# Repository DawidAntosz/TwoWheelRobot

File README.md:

# TwoWheelRobot
Differential wheeled robot

This project is focused on building a two-wheel differential robot with the ability to control and navigate in area.

## Project Structure
The project is organized into the following directories:

- `src/`: Contains the source code for the project.
  - `arduino/`: Source code using the Arduino framework (PlatformIO).
  - `esp_rtos_sdk/`: (For future development of the project using the ESP8266 RTOS SDK).

##### Control page:
<p align="center">
<!--     -->
   
<!--     -->
</p>

##### Robot V1:

##### Math model

$$
\dot{x} = \frac{R}{2}(v_r + v_\ell)\cos\phi
$$
$$
\dot{y} = \frac{R}{2}(v_r + v_\ell)\sin\phi
$$
$$
\dot{\phi} = \frac{R}{L}(v_r - v_\ell)
$$

$$
\dot{x} = v\cos\phi
$$
$$
\dot{y} = v\sin\phi
$$
$$
\dot{\phi} = \omega
$$

$$
v = \frac{R}{2}(v_r + v_\ell) \implies \frac{2v}{R} = v_r + v_\ell
$$

$$
\omega = \frac{R}{L}(v_r - v_\ell) \implies \frac{\omega L}{R} = v_r - v_\ell
$$

$$
\ v_r = \\frac{2v + \\omega L}{2R} \\\ 
$$
$$
 v_l = \\frac{2v - \\omega L}{2R} \
$$

Description parameters:
- \( v_r \): the speed of the right wheel
- \( v_\ell \): the speed of the left wheel
- \( R \): the radius of the wheel
- \( L \): the distance between the wheels
- \( $$\omega$$ \): the angular velocity of the robot

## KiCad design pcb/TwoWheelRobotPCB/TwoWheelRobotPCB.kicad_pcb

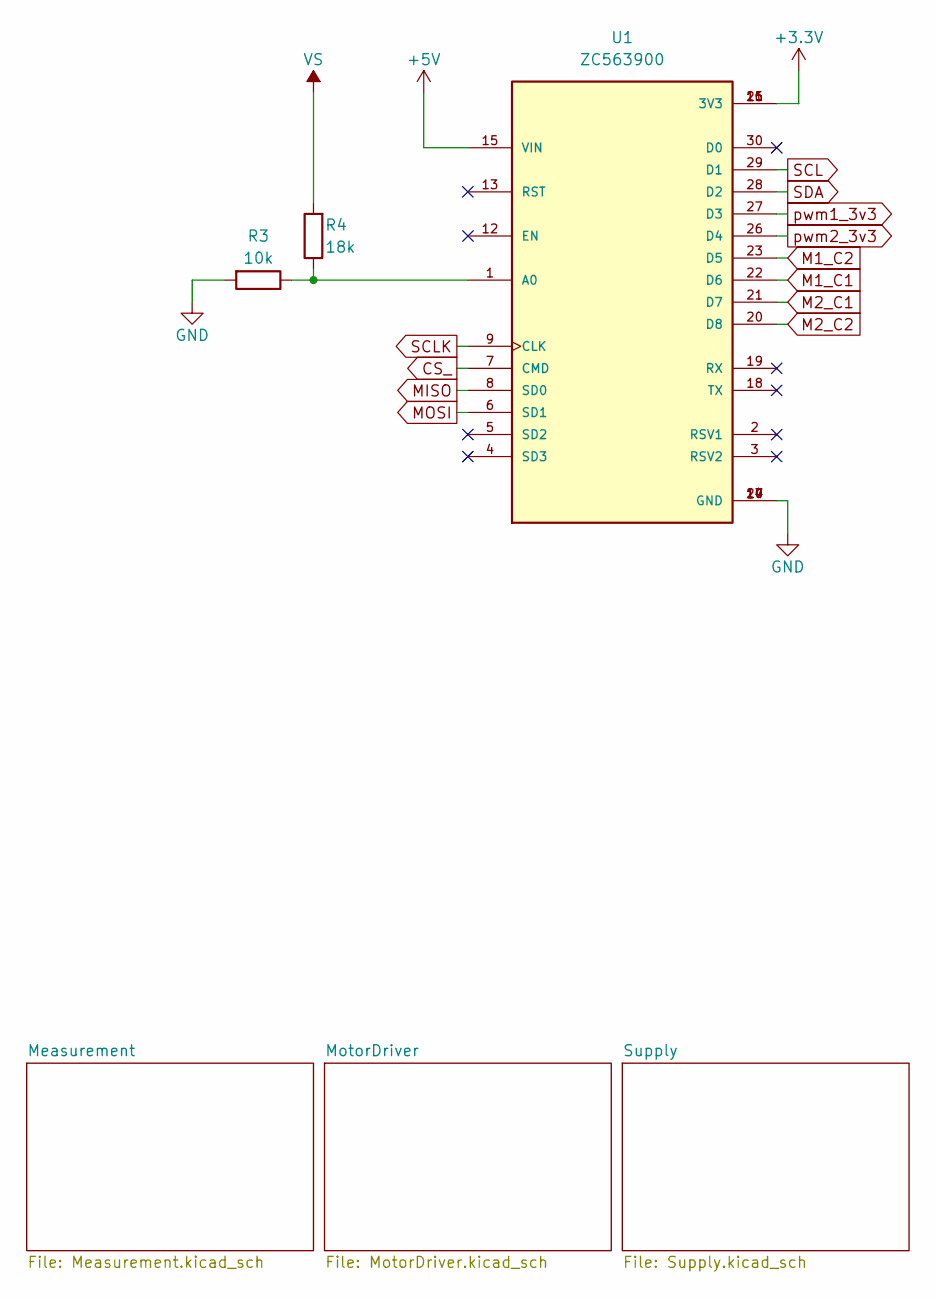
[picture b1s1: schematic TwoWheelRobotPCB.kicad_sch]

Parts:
R3: 10k; R_0805_2012Metric
R4: 18k; R_0805_2012Metric
U1: ZC563900; MODULE_ZC563900; PARTREV 1.0

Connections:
+3V3: U1.11 (3V3), U1.16 (3V3), U1.25 (3V3); also elsewhere on the board
+5V: U1.15 (VIN); also elsewhere on the board
CS_: U1.7 (CMD); also elsewhere on the board
GND: R3.2, U1.10 (GND), U1.14 (GND), U1.17 (GND), U1.24 (GND); also elsewhere on the board
M1_C1: U1.22 (D6); also elsewhere on the board
M1_C2: U1.23 (D5); also elsewhere on the board
M2_C1: U1.21 (D7); also elsewhere on the board
M2_C2: U1.20 (D8); also elsewhere on the board
MISO: U1.8 (SD0); also elsewhere on the board
MOSI: U1.6 (SD1); also elsewhere on the board
unnamed: R3.1, R4.1, U1.1 (A0)
SCL: U1.29 (D1); also elsewhere on the board
SCLK: U1.9 (CLK); also elsewhere on the board
SDA: U1.28 (D2); also elsewhere on the board
VS: R4.2; also elsewhere on the board
pwm1_3v3: U1.27 (D3); also elsewhere on the board
pwm2_3v3: U1.26 (D4); also elsewhere on the board

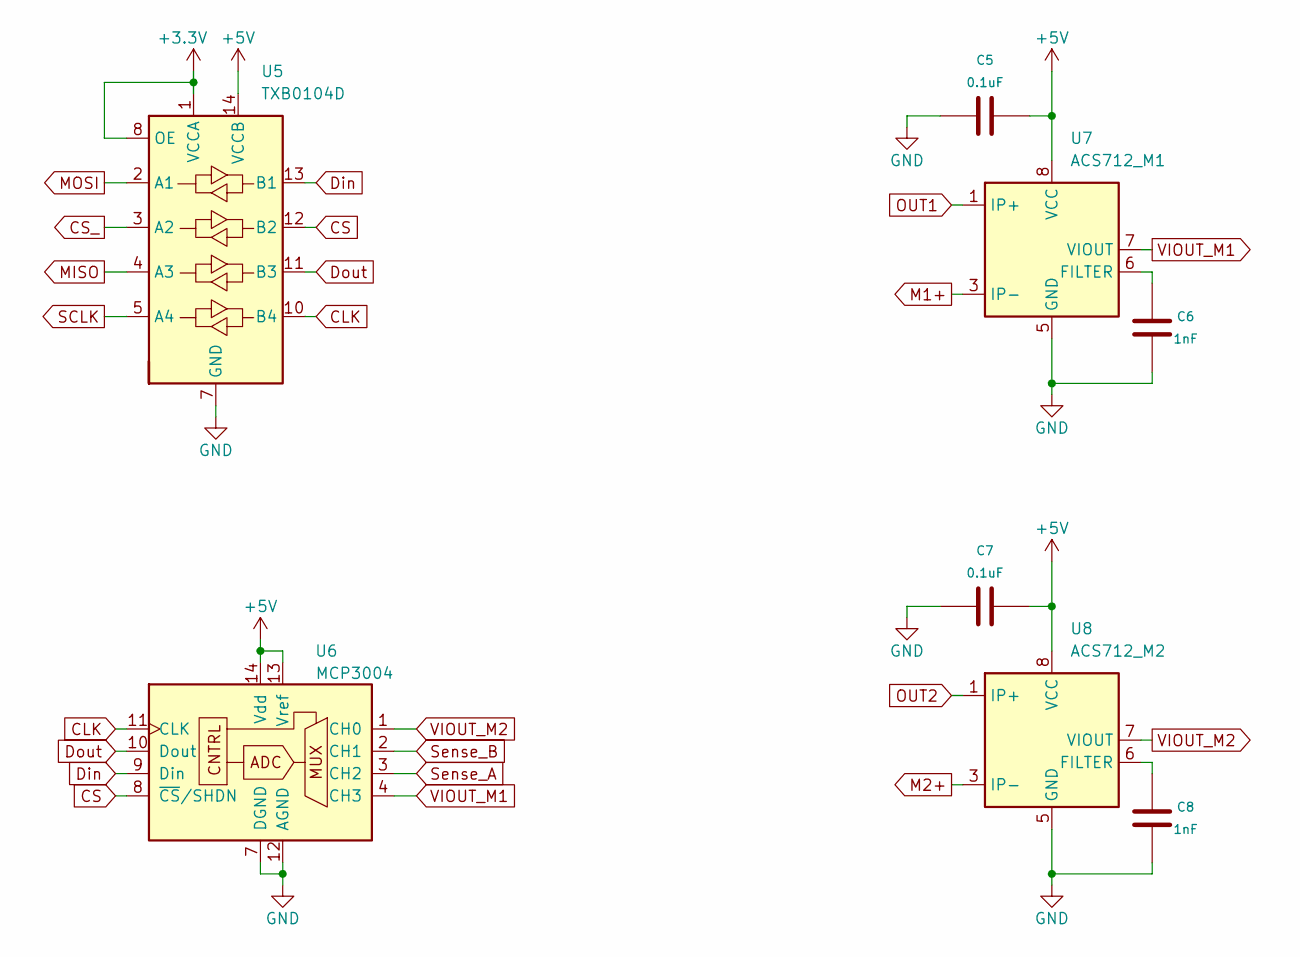
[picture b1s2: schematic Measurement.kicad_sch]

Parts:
C5, C7: 0.1uF; C_0805_2012Metric
C6, C8: 1nF; C_0805_2012Metric
U5: TXB0104D; SOP65P640X120-14N
U6: MCP3004; SOIC127P600X175-14N
U7: ACS712_M1; SOIC-8_3.9x4.9mm_P1.27mm
U8: ACS712_M2; SOIC-8_3.9x4.9mm_P1.27mm

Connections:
+3V3: U5.1 (VCCA), U5.8 (OE); also elsewhere on the board
+5V: C5.1, C7.1, U5.14 (VCCB), U6.13 (Vref), U6.14 (Vdd), U7.8 (VCC), U8.8 (VCC); also elsewhere on the board
CLK: U5.10 (B4), U6.11 (CLK)
CS: U5.12 (B2), U6.8 (~CS/SHDN)
CS_: U5.3 (A2); also elsewhere on the board
Din: U5.13 (B1), U6.9 (Din)
Dout: U5.11 (B3), U6.10 (Dout)
GND: C5.2, C6.2, C7.2, C8.2, U5.7 (GND), U6.7 (DGND), U6.12 (AGND), U7.5 (GND), U8.5 (GND); also elsewhere on the board
M1+: U7.3 (IP-), U7.4 (IP-); also elsewhere on the board
M2+: U8.3 (IP-), U8.4 (IP-); also elsewhere on the board
MISO: U5.4 (A3); also elsewhere on the board
MOSI: U5.2 (A1); also elsewhere on the board
unnamed: C6.1, U7.6 (FILTER)
unnamed: C8.1, U8.6 (FILTER)
OUT1: U7.1 (IP+), U7.2 (IP+); also elsewhere on the board
OUT2: U8.1 (IP+), U8.2 (IP+); also elsewhere on the board
SCLK: U5.5 (A4); also elsewhere on the board
Sense_A: U6.3 (CH2); also elsewhere on the board
Sense_B: U6.2 (CH1); also elsewhere on the board
VIOUT_M1: U6.4 (CH3), U7.7 (VIOUT)
VIOUT_M2: U6.1 (CH0), U8.7 (VIOUT)

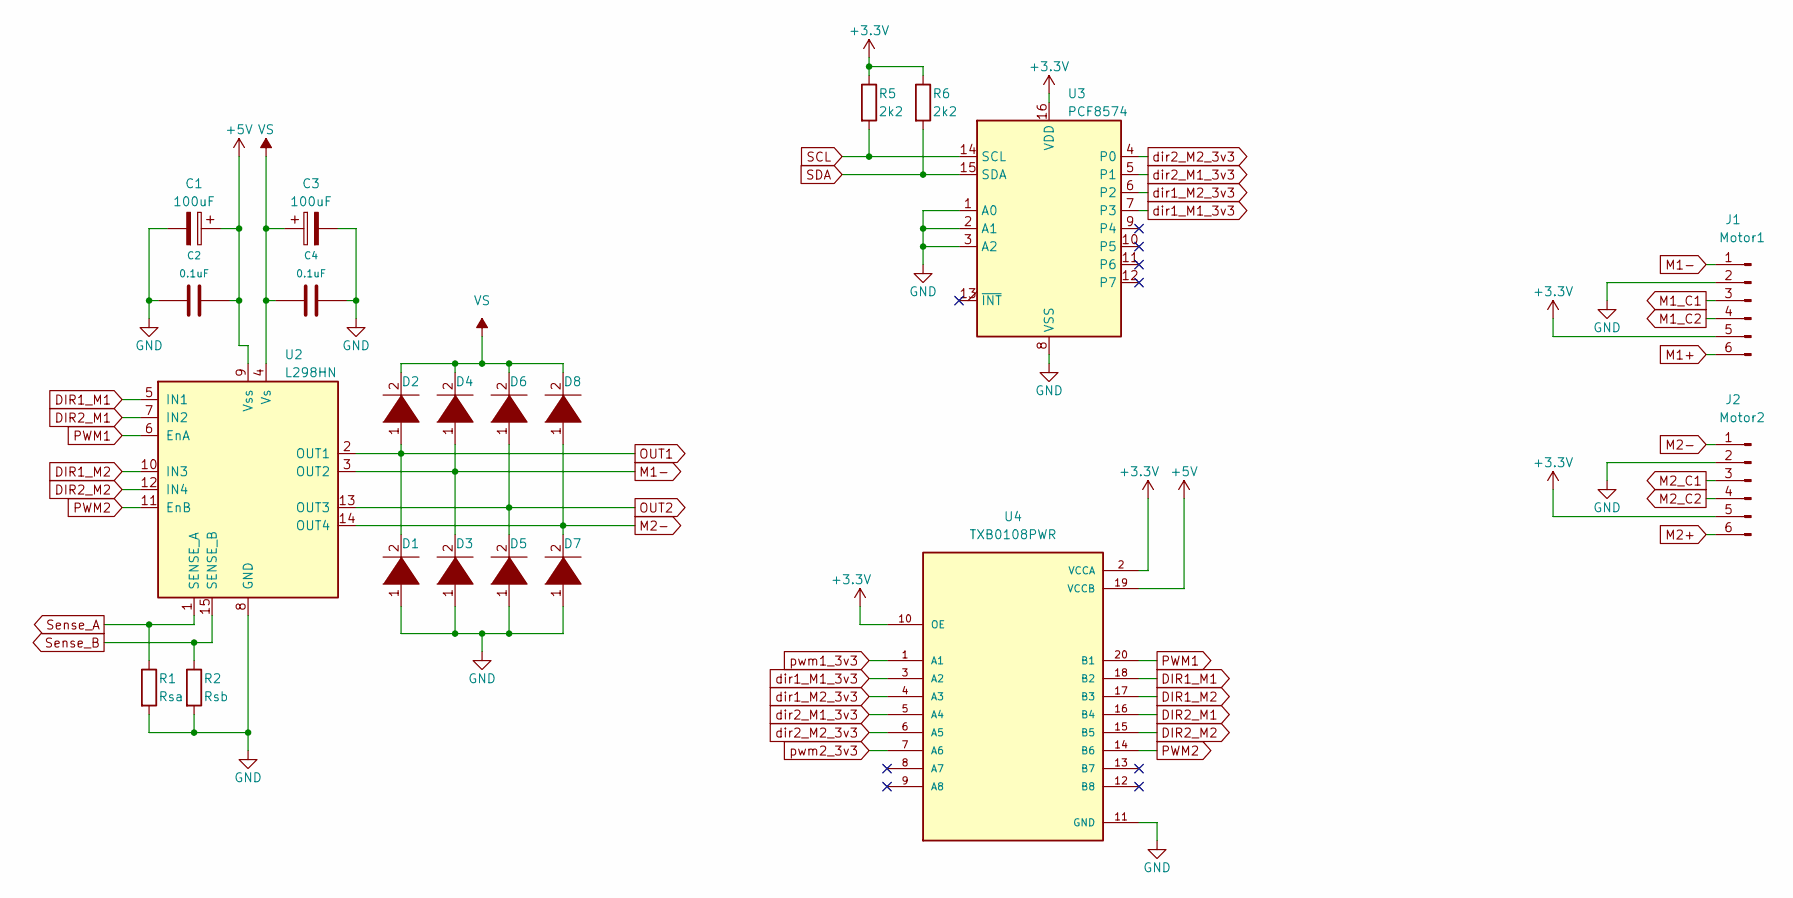
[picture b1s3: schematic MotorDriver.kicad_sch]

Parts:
C1, C3: 100uF; CP_Radial_D6.3mm_P2.50mm
C2, C4: 0.1uF; C_Disc_D4.3mm_W1.9mm_P5.00mm
D1, D2, D3, D4, D5, D6, D7, D8: DIODE; D_A-405_P10.16mm_Horizontal
J1: Motor1; PinHeader_1x06_P2.54mm_Vertical
J2: Motor2; PinHeader_1x06_P2.54mm_Vertical
R1: Rsa; R_0805_2012Metric
R2: Rsb; R_0805_2012Metric
R5, R6: 2k2; R_0805_2012Metric
U2: L298HN; TO-220-15_P2.54x2.54mm_StaggerOdd_Lead4.58mm_Vertical
U3: PCF8574; SO16W
U4: TXB0108PWR; SOP65P640X120-20N; PARTREV H

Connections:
+3V3: J1.5, J2.5, R5.1, R6.1, U3.16 (VDD), U4.2 (VCCA), U4.10 (OE); also elsewhere on the board
+5V: C1.1, C2.1, U2.9 (Vss), U4.19 (VCCB); also elsewhere on the board
DIR1_M1: U2.5 (IN1), U4.18 (B2)
DIR1_M2: U2.10 (IN3), U4.17 (B3)
DIR2_M1: U2.7 (IN2), U4.16 (B4)
DIR2_M2: U2.12 (IN4), U4.15 (B5)
GND: C1.2, C2.2, C3.2, C4.1, D1.1 (K), D3.1 (K), D5.1 (K), D7.1 (K), J1.2, J2.2, R1.2, R2.2, U2.8 (GND), U3.1 (A0), U3.2 (A1), U3.3 (A2), U3.8 (VSS), U4.11 (GND); also elsewhere on the board
M1+: J1.6; also elsewhere on the board
M1-: D3.2 (A), D4.1 (K), J1.1, U2.3 (OUT2)
M1_C1: J1.3; also elsewhere on the board
M1_C2: J1.4; also elsewhere on the board
M2+: J2.6; also elsewhere on the board
M2-: D7.2 (A), D8.1 (K), J2.1, U2.14 (OUT4)
M2_C1: J2.3; also elsewhere on the board
M2_C2: J2.4; also elsewhere on the board
OUT1: D1.2 (A), D2.1 (K), U2.2 (OUT1); also elsewhere on the board
OUT2: D5.2 (A), D6.1 (K), U2.13 (OUT3); also elsewhere on the board
PWM1: U2.6 (EnA), U4.20 (B1)
PWM2: U2.11 (EnB), U4.14 (B6)
SCL: R5.2, U3.14 (SCL); also elsewhere on the board
SDA: R6.2, U3.15 (SDA); also elsewhere on the board
Sense_A: R1.1, U2.1 (SENSE_A); also elsewhere on the board
Sense_B: R2.1, U2.15 (SENSE_B); also elsewhere on the board
VS: C3.1, C4.2, D2.2 (A), D4.2 (A), D6.2 (A), D8.2 (A), U2.4 (Vs); also elsewhere on the board
dir1_M1_3v3: U3.7 (P3), U4.3 (A2)
dir1_M2_3v3: U3.6 (P2), U4.4 (A3)
dir2_M1_3v3: U3.5 (P1), U4.5 (A4)
dir2_M2_3v3: U3.4 (P0), U4.6 (A5)
pwm1_3v3: U4.1 (A1); also elsewhere on the board
pwm2_3v3: U4.7 (A6); also elsewhere on the board

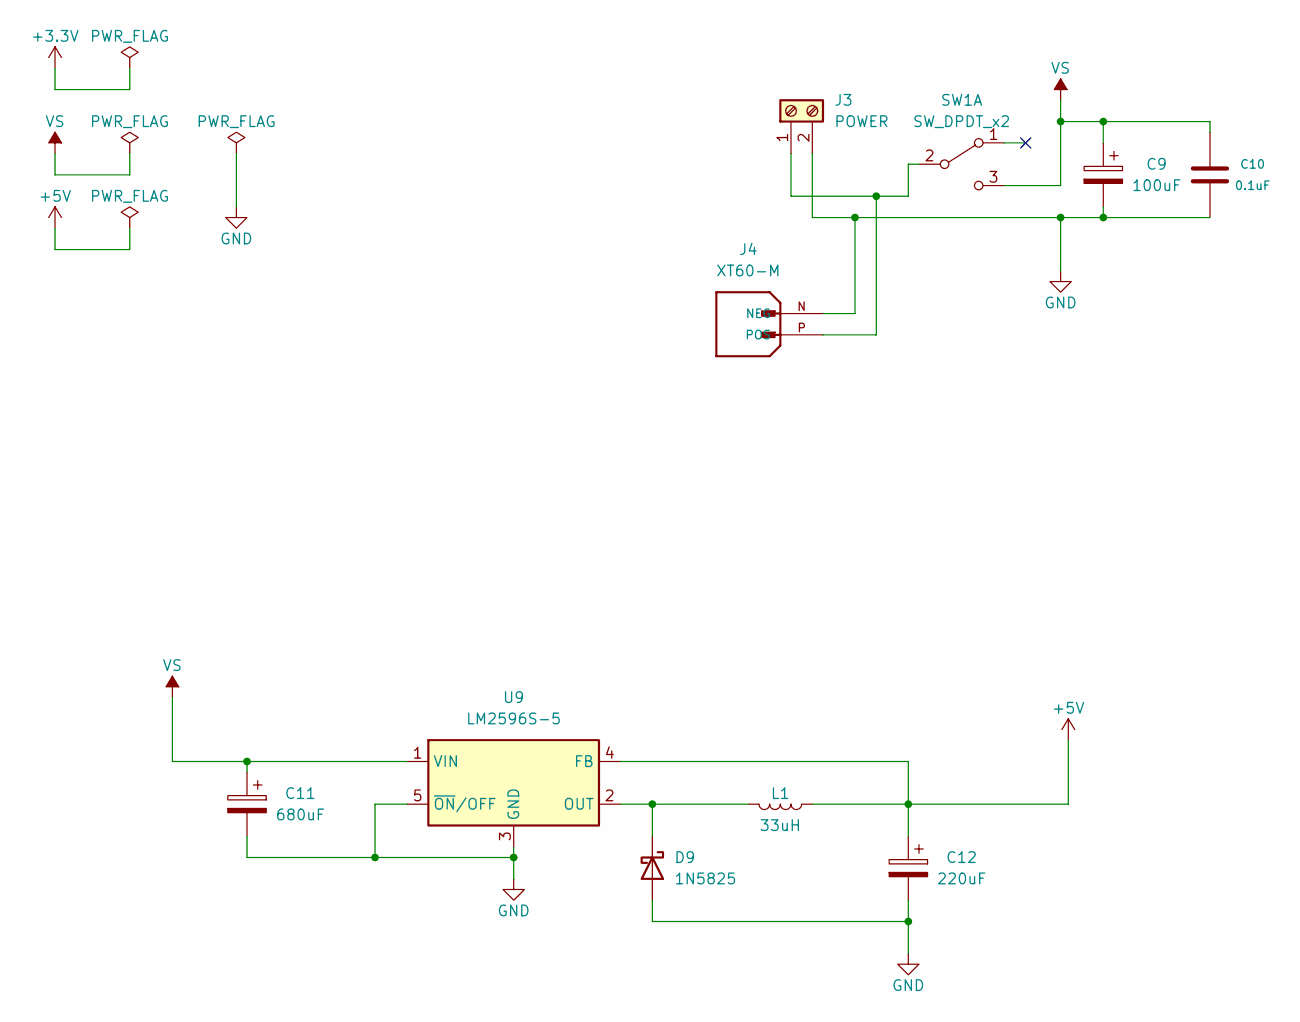
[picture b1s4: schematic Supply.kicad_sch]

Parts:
C9: 100uF; CP_Radial_D6.3mm_P2.50mm
C10: 0.1uF; C_Disc_D4.3mm_W1.9mm_P5.00mm
C11: 680uF; CP_Elec_8x6.9
C12: 220uF; CP_Elec_8x6.9
D9: 1N5825; D_2010_5025Metric_Pad1.52x2.65mm_HandSolder
J3: POWER; TerminalBlock_RND_205-00001_1x02_P5.00mm_Horizontal
J4: XT60-M; AMASS_XT60-M; PARTREV V1.2
L1: 33uH; L_Bourns_SRP1245A
SW1: SW_DPDT_x2; SW_PUSH_E-Switch_FS5700DP_DPDT
U9: LM2596S-5; TO-263-5_TabPin3

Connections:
+5V: C12.1, L1.1, U9.4 (FB); also elsewhere on the board
GND: C9.2, C10.1, C11.2, C12.2, D9.2 (A), J3.2, J4.N (NEG), U9.3 (GND), U9.5 (~ON/OFF); also elsewhere on the board
unnamed: D9.1 (K), L1.2, U9.2 (OUT)
unnamed: J3.1, J4.P (POS), SW1.2 (B)
VS: C9.1, C10.2, C11.1, SW1.3 (C), U9.1 (VIN); also elsewhere on the board

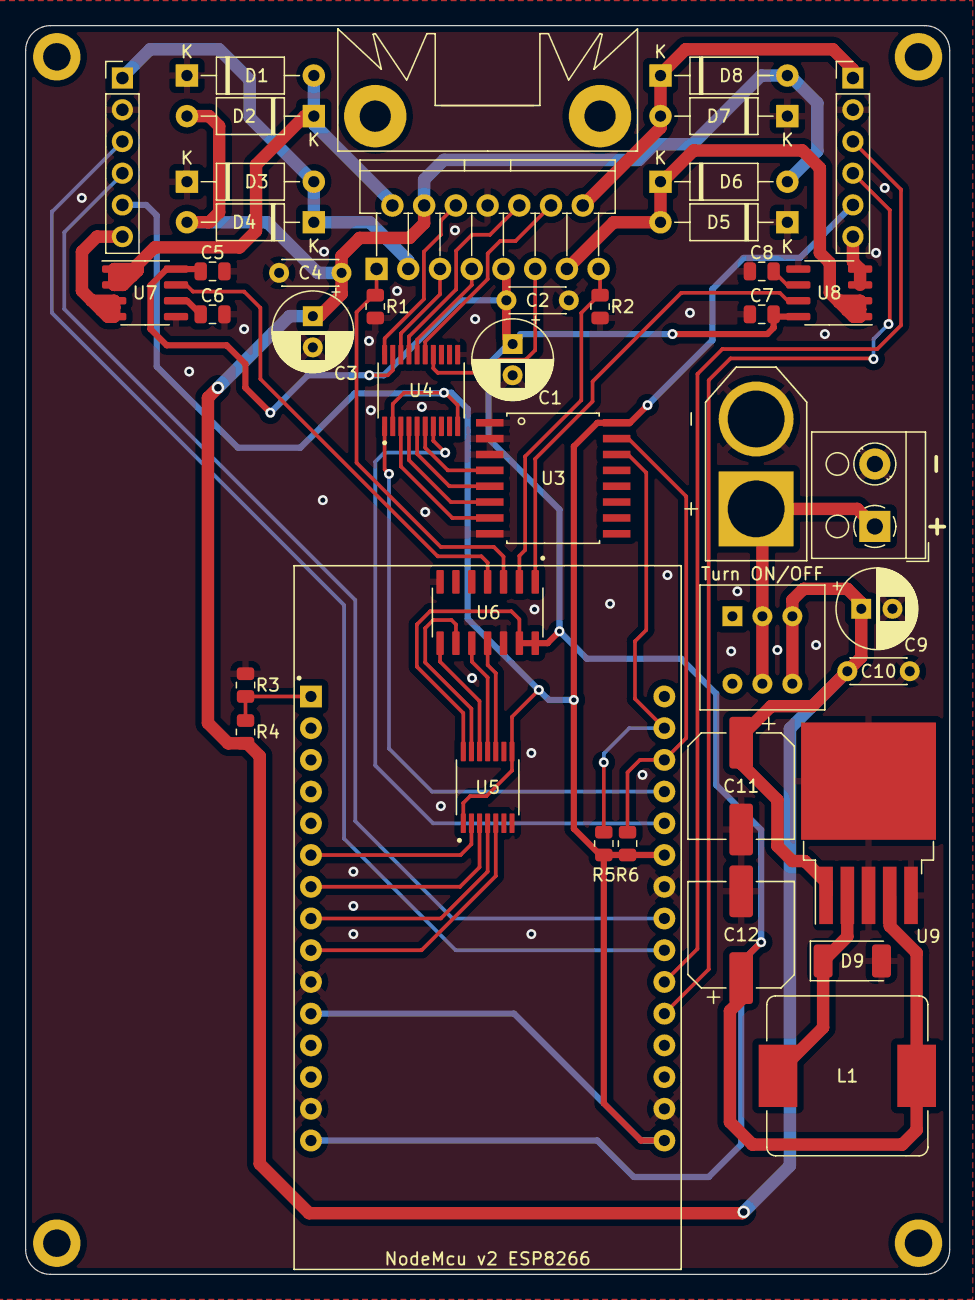
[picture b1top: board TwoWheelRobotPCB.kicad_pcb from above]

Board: 2 copper layers, 74.0 x 100.0 mm, 42 parts (0 on the bottom side), 45 nets.

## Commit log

2024-11-14 init
2025-01-10 init repository
2025-01-10 header file
2025-01-11 calculate current position function
2025-01-12 WiFi manager class to host website by SPIFFS
2025-01-12 git ignore
2025-01-12 git ignore wifi conf
2025-01-12 Usunięcie pliku WiFiConfig.hpp z historii Git
2025-01-12 wi fi data template
2025-01-12 rm template
2025-01-12 wifi manager class
2025-01-20 robot movement view
2025-01-20 movement robot on page working
2025-01-23 robotView class && update pcb
2025-02-02 pcb update
2025-02-02 update pcb
2025-03-03 pcb finish
